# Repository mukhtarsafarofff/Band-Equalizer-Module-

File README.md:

(ENG) The human audible range is from about 20Hz to 20K Hz. So when you are listening to music, you are hearing the sound waves somewhere within that frequency range. With a 3 band equalizer we break up the spectrum in three sections : 1) the bass for the low sounds   2) the mid for the mid range    3) the treble for the high frequenceies . For each of these 3 bands, I create filters in our circuit to control their respective audible volumes. I can pump up that low frequency bass sound or increase those treble high sounds.  The outputted audio would normally be passed on to an audio amplifier such as the LM386. The audio amplifer would then be responsible for amplifying the signal so it can be heard on a speaker. The reason we need an amplifer between the equalizer and speaker is because the direct signal from a microphone or audio source 

(DEU) Der für den Menschen hörbare Bereich liegt zwischen etwa 20 Hz und 20 kHz. Wenn Sie also Musik hören, hören Sie die Schallwellen irgendwo innerhalb dieses Frequenzbereichs. Mit einem 3-Band-Equalizer teilen wir das Spektrum in drei Abschnitte auf: 1) den Bass für die tiefen Töne, 2) die Mitte für den mittleren Bereich 3) die Höhen für die hohen Frequenzen. Für jedes dieser drei Bänder erstelle ich Filter in unserer Schaltung, um deren jeweilige hörbare Lautstärke zu steuern. Ich kann den Tiefton-Bassklang aufpumpen oder die hohen Höhentöne anheben. Der ausgegebene Ton wird normalerweise an einen Audioverstärker wie den LM386 weitergeleitet. Der Audioverstärker wäre dann dafür verantwortlich, das Signal zu verstärken, damit es über einen Lautsprecher gehört werden kann.  Der Grund, warum wir einen Verstärker zwischen dem Equalizer und dem Lautsprecher benötigen, liegt darin, dass das direkte Signal von einem Mikrofon oder einer Audioquelle normalerweise zu klein ist, um direkt eingespeist zu werden Ein Sprecher.

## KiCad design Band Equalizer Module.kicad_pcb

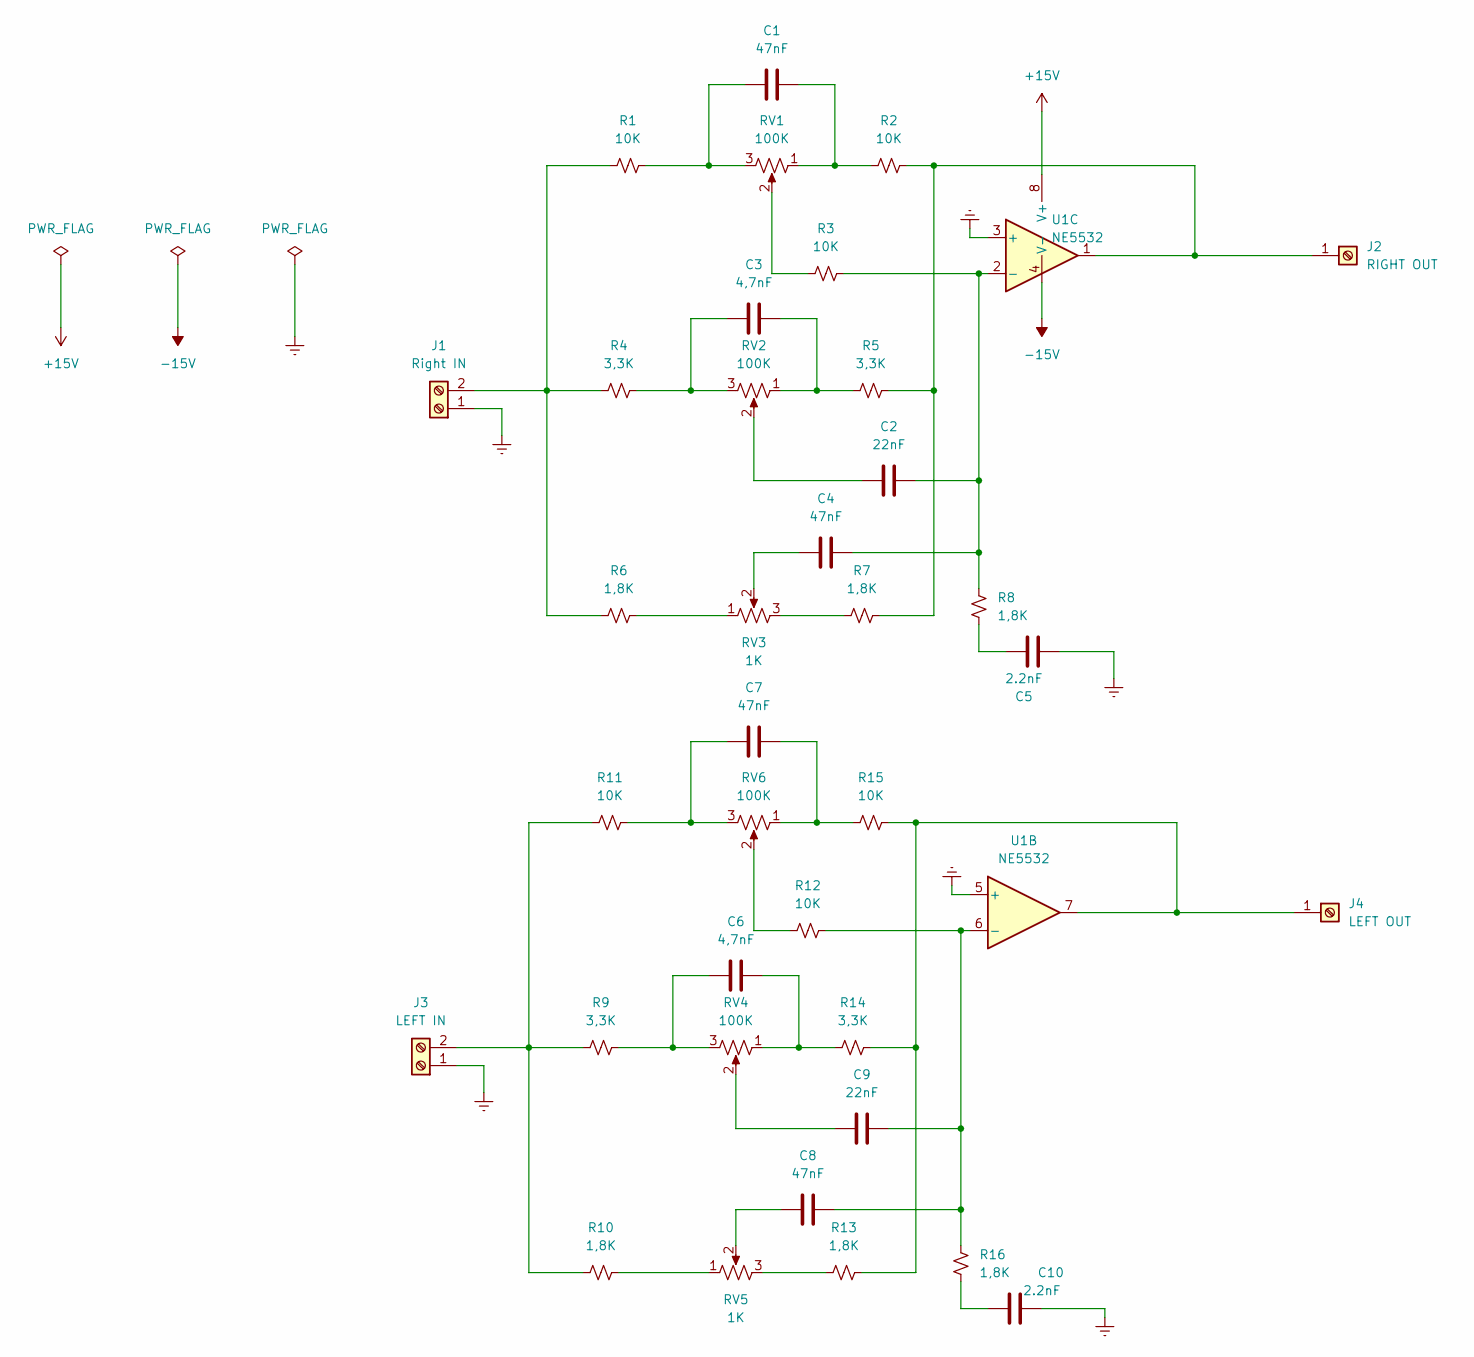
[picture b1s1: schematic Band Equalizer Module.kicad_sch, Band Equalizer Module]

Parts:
C1, C4, C7, C8: 47nF; C_Disc_D8.0mm_W5.0mm_P7.50mm
C2, C9: 22nF; C_Disc_D8.0mm_W5.0mm_P7.50mm
C3, C6: 4,7nF; C_Disc_D8.0mm_W5.0mm_P7.50mm
C5, C10: 2.2nF; C_Disc_D8.0mm_W5.0mm_P7.50mm
J1: Right IN; TerminalBlock_bornier-2_P5.08mm
J2: RIGHT OUT; TerminalBlock_MetzConnect_360271_1x01_Horizontal_ScrewM3.0_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
J3: LEFT IN; TerminalBlock_bornier-2_P5.08mm
J4: LEFT OUT; TerminalBlock_MetzConnect_360271_1x01_Horizontal_ScrewM3.0_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
R1, R2, R3, R11, R12, R15: 10K; R_Axial_DIN0414_L11.9mm_D4.5mm_P15.24mm_Horizontal
R4, R5, R9, R14: 3,3K; R_Axial_DIN0414_L11.9mm_D4.5mm_P15.24mm_Horizontal
R6, R7, R8, R10, R13, R16: 1,8K; R_Axial_DIN0414_L11.9mm_D4.5mm_P15.24mm_Horizontal
RV1, RV2, RV4, RV6: 100K; Potentiometer_Vishay_148-149_Single_Horizontal
RV3, RV5: 1K; Potentiometer_Vishay_148-149_Single_Horizontal
U1: NE5532; DIP-8_W7.62mm

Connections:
+15V: U1.8 (V+)
-15V: U1.4 (V-)
Earth: C5.2, C10.2, J1.1, J3.1, U1.3 (+), U1.5 (+)
unnamed: C1.1, R1.2, RV1.3
unnamed: C1.2, R2.1, RV1.1
unnamed: C2.1, RV2.2
unnamed: C3.1, R4.2, RV2.3
unnamed: C3.2, R5.1, RV2.1
unnamed: C4.1, RV3.2
unnamed: C5.1, R8.2
unnamed: C6.1, R9.2, RV4.3
unnamed: C6.2, R14.1, RV4.1
unnamed: C7.1, R11.2, RV6.3
unnamed: C7.2, R15.1, RV6.1
unnamed: C8.1, RV5.2
unnamed: C9.1, RV4.2
unnamed: C10.1, R16.2
unnamed: J1.2, R1.1, R4.1, R6.1
unnamed: J2.1, R2.2, R5.2, R7.2, U1.1
unnamed: J3.2, R9.1, R10.1, R11.1
unnamed: J4.1, R13.2, R14.2, R15.2, U1.7
unnamed: R3.1, RV1.2
unnamed: R6.2, RV3.1
unnamed: R7.1, RV3.3
unnamed: R10.2, RV5.1
unnamed: R12.1, RV6.2
unnamed: R13.1, RV5.3
unnamed: C2.2, C4.2, R3.2, R8.1, U1.2 (-)
unnamed: C8.2, C9.2, R12.2, R16.1, U1.6 (-)

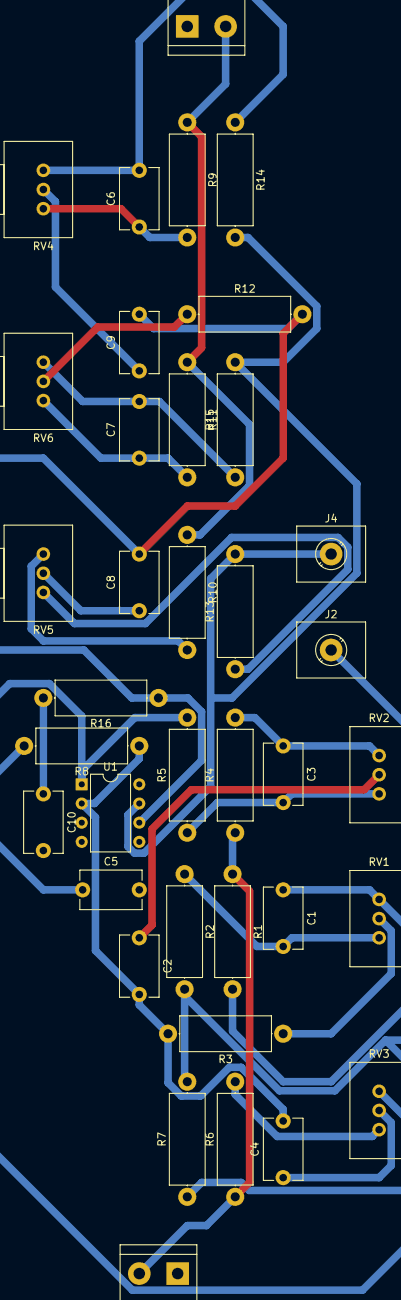
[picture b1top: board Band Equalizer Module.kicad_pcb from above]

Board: 2 copper layers, 37 parts (0 on the bottom side), 27 nets.

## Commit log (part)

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2024-04-01 Band Equalizer Module is accomplished
